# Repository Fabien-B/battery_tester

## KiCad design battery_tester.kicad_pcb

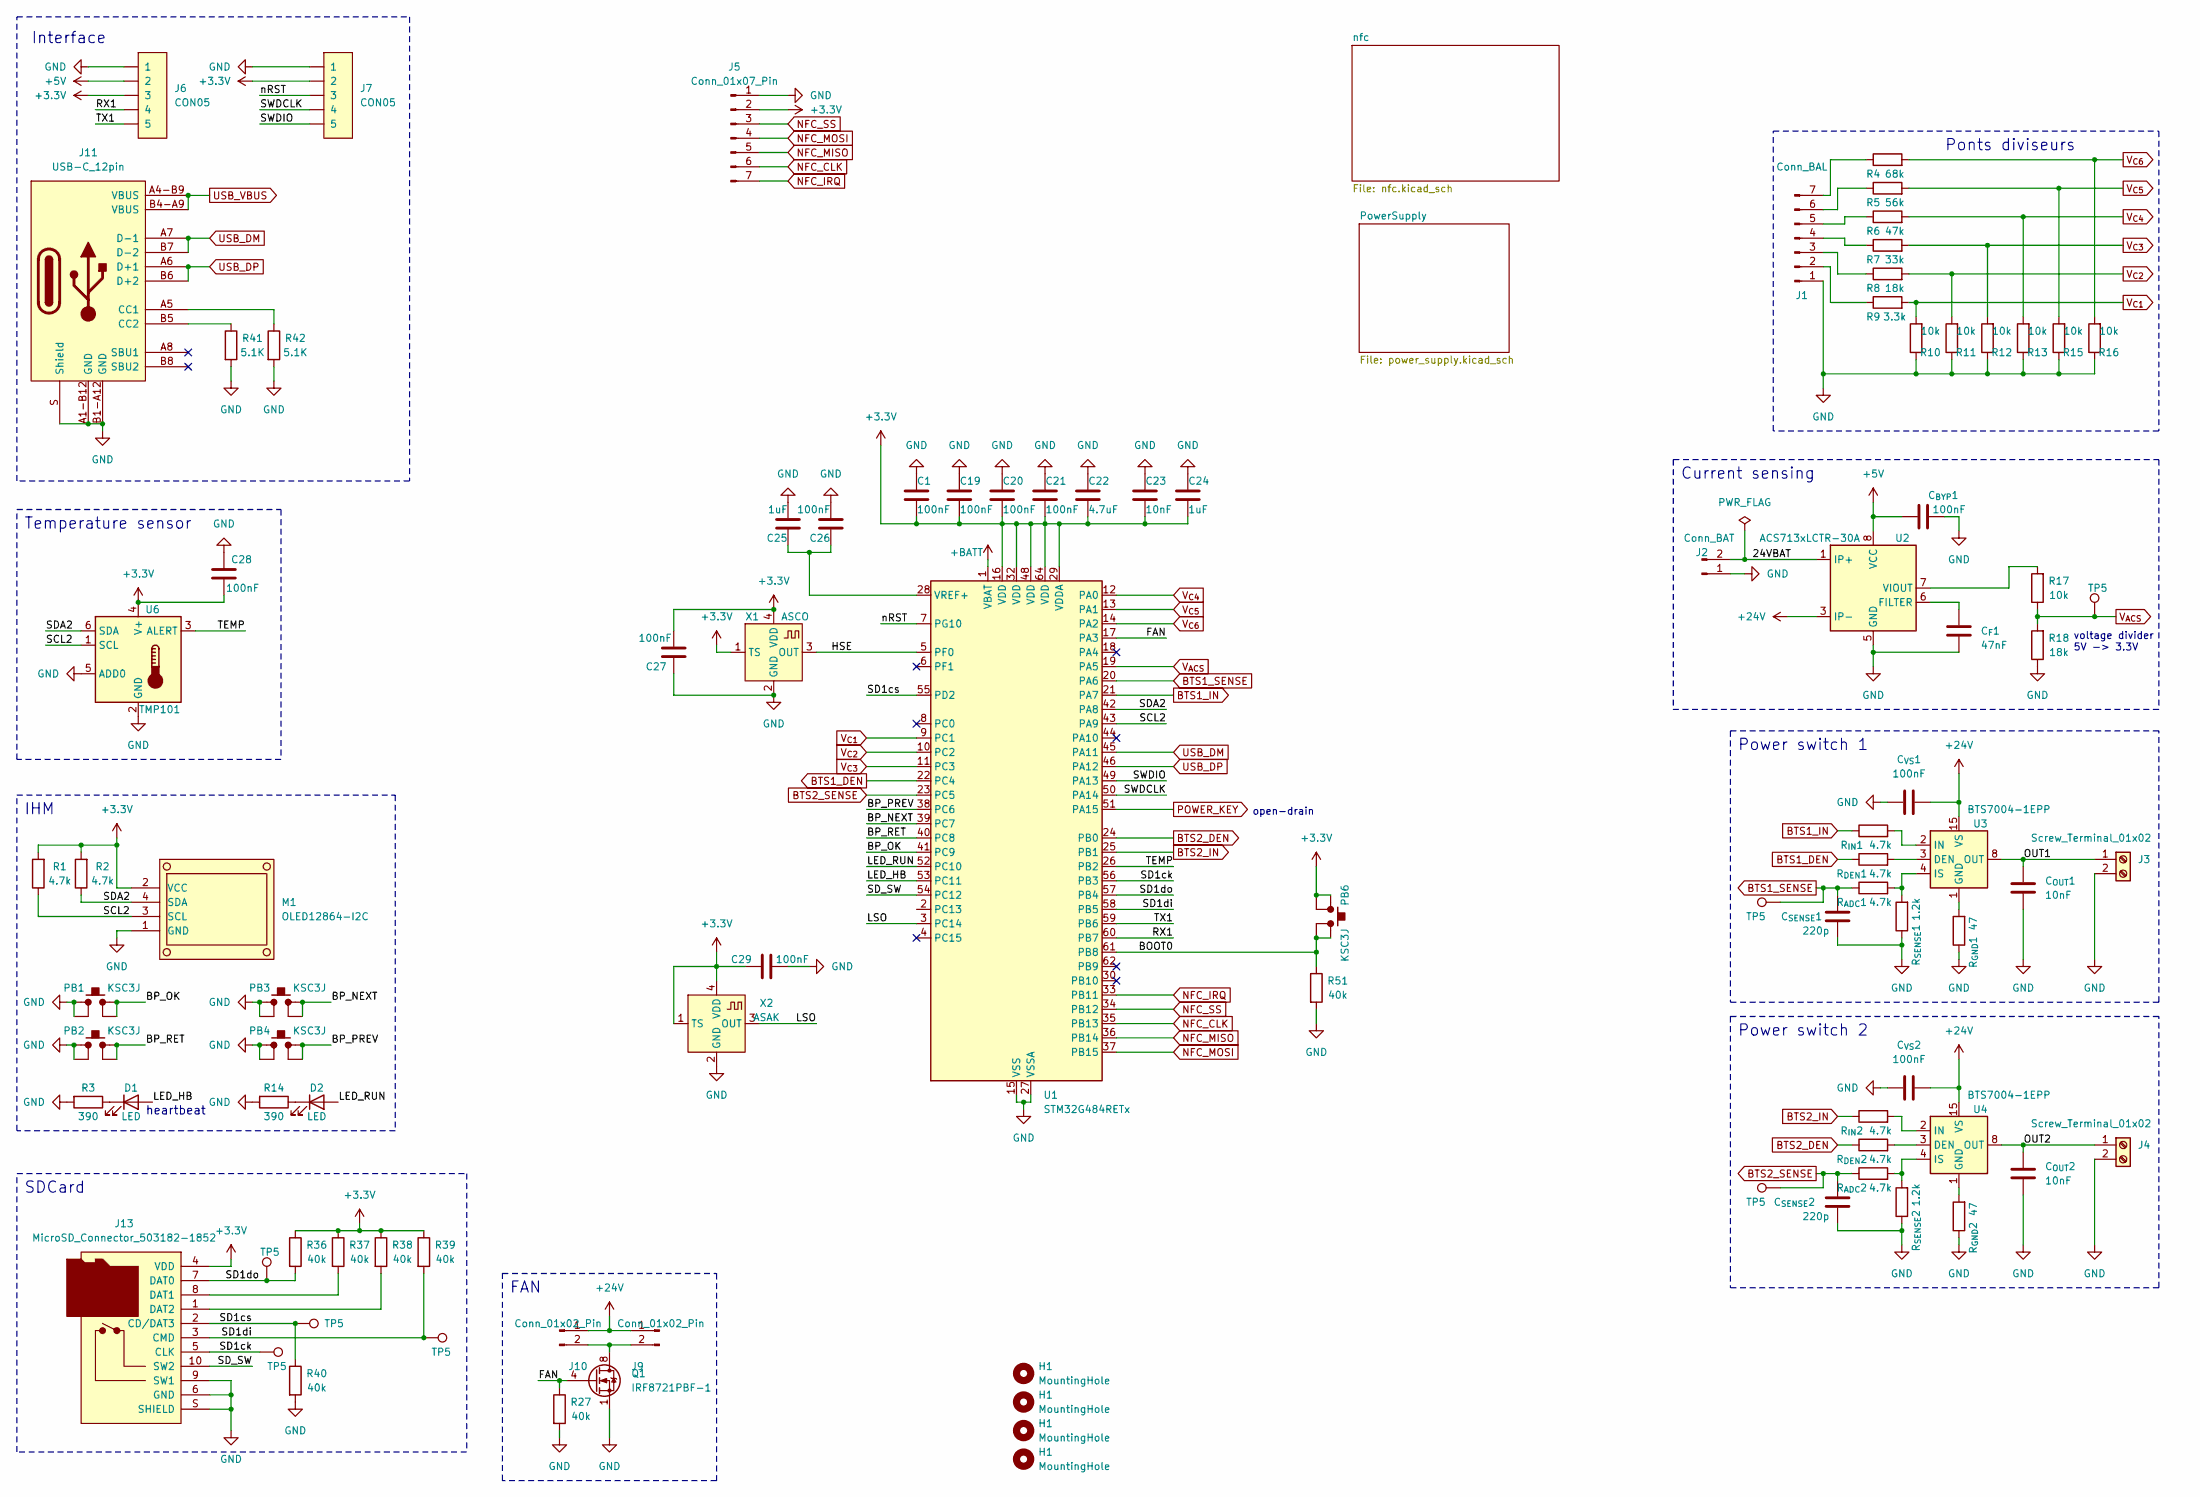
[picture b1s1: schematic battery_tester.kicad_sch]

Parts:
C1, C19, C20, C21, C26, C27, C28, C29: 100nF; C_0603_1608Metric
C22: 4.7uF; C_0603_1608Metric
C23: 10nF; C_0603_1608Metric
C24, C25: 1uF; C_0603_1608Metric
C_{BYP}1: 100nF; C_0603_1608Metric
C_{F}1: 47nF; C_0603_1608Metric
C_{OUT}1, C_{OUT}2: 10nF; C_0603_1608Metric
C_{SENSE}1, C_{SENSE}2: 220p; C_0603_1608Metric
C_{VS}1, C_{VS}2: 100nF; C_0603_1608Metric
D1, D2: LED; LED_0603_1608Metric
H1: MountingHole; MountingHole_3.2mm_M3
J1: Conn_BAL; JST_XH_S7B-XH-A_1x07_P2.50mm_Horizontal
J2: Conn_BAT; AMASS_XT60IPW-M_1x03_P7.20mm_Horizontal
J3, J4: Screw_Terminal_01x02; TerminalBlock_bornier-2_P5.08mm
J5: Conn_01x07_Pin; PicoBlade_53398-0771
J6, J7: CON05; PicoBlade_53398-0571
J9, J10: Conn_01x02_Pin; PinHeader_1x02_P2.54mm_Horizontal
J11: USB-C_12pin; USB-C_HRO_C-31-M-12
J13: MicroSD_Connector_503182-1852; MicroSD_503182-1852
M1: OLED12864-I2C
PB1, PB2, PB3, PB4, PB6: KSC3J
Q1: IRF8721PBF-1; SOIC-8_3.9x4.9mm_P1.27mm
R1, R2: 4.7k; R_0603_1608Metric
R3, R14: 390; R_0603_1608Metric
R4: 68k; R_0603_1608Metric
R5: 56k; R_0603_1608Metric
R6: 47k; R_0603_1608Metric
R7: 33k; R_0603_1608Metric
R8, R18: 18k; R_0603_1608Metric
R9: 3.3k; R_0603_1608Metric
R10, R11, R12, R13, R15, R16, R17: 10k; R_0603_1608Metric
R27, R36, R37, R38, R39, R40, R51: 40k; R_0603_1608Metric
R41, R42: 5.1K; R_0603_1608Metric
R_{ADC}1, R_{ADC}2: 4.7k; R_0603_1608Metric
R_{DEN}1, R_{DEN}2: 4.7k; R_0603_1608Metric
R_{GND}1, R_{GND}2: 47; R_0603_1608Metric
R_{IN}1, R_{IN}2: 4.7k; R_0603_1608Metric
R_{SENSE}1, R_{SENSE}2: 1.2k; R_0603_1608Metric
TP5: TestPoint; TestPoint_Pad_D2.0mm
U1: STM32G484RETx; LQFP-64_10x10mm_P0.5mm
U2: ACS713xLCTR-30A; SOIC-8_3.9x4.9mm_P1.27mm
U3, U4: BTS7004-1EPP; Infineon_PG-TSDSO-14-22
U6: TMP101; SOT-23-6
X1: ASCO; Osc_ASCO
X2: ASAK; Osc_ASAK

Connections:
+5V: C_{BYP}1.1, J6.2, U2.8 (VCC); also elsewhere on the board
+24V: C_{VS}1.1, C_{VS}2.1, J9.1, J10.1, U2.3 (IP-), U2.4 (IP-), U3.15 (VS), U4.15 (VS)
+BATT: U1.1 (VBAT); also elsewhere on the board
/24VBAT: J2.2, U2.1 (IP+), U2.2 (IP+)
/BP_NEXT: PB3.2, PB3.3, U1.39 (PC7)
/BP_OK: PB1.2, PB1.3, U1.41 (PC9)
/BP_PREV: PB4.2, PB4.3, U1.38 (PC6)
/BP_RET: PB2.2, PB2.3, U1.40 (PC8)
/FAN: Q1.4 (G), R27.1, U1.17 (PA3)
/HSE: U1.5 (PF0), X1.3 (OUT)
/LED_HB: D1.2 (A), U1.53 (PC11)
/LED_RUN: D2.2 (A), U1.52 (PC10)
/LSO: U1.3 (PC14), X2.3 (OUT)
/OUT1: C_{OUT}1.1, J3.1, U3.8 (OUT), U3.9 (OUT), U3.10 (OUT), U3.12 (OUT), U3.13 (OUT), U3.14 (OUT)
/OUT2: C_{OUT}2.1, J4.1, U4.8 (OUT), U4.9 (OUT), U4.10 (OUT), U4.12 (OUT), U4.13 (OUT), U4.14 (OUT)
/RX1: J6.4, U1.60 (PB7)
/SCL2: M1.3 (SCL), R1.1, U1.43 (PA9), U6.1 (SCL)
/SD1ck: J13.5 (CLK), U1.56 (PB3); also elsewhere on the board
/SD1cs: J13.2 (CD/DAT3), R40.1, U1.55 (PD2); also elsewhere on the board
/SD1di: J13.3 (CMD), R39.2, U1.58 (PB5); also elsewhere on the board
/SD1do: J13.7 (DAT0), R36.2, U1.57 (PB4); also elsewhere on the board
/SDA2: M1.4 (SDA), R2.1, U1.42 (PA8), U6.6 (SDA)
/SD_SW: J13.10 (SW2), U1.54 (PC12)
/SWDCLK: J7.4, U1.50 (PA14)
/SWDIO: J7.5, U1.49 (PA13)
/TEMP: U1.26 (PB2), U6.3 (ALERT)
/TX1: J6.5, U1.59 (PB6)
/nRST: J7.3, U1.7 (PG10)
BTS1_DEN: R_{DEN}1.1, U1.22 (PC4)
BTS1_IN: R_{IN}1.1, U1.21 (PA7)
BTS1_SENSE: C_{SENSE}1.1, R_{ADC}1.1, U1.20 (PA6); also elsewhere on the board
BTS2_DEN: R_{DEN}2.1, U1.24 (PB0)
BTS2_IN: R_{IN}2.1, U1.25 (PB1)
BTS2_SENSE: C_{SENSE}2.1, R_{ADC}2.1, U1.23 (PC5); also elsewhere on the board
NFC_CLK: U1.35 (PB13); also elsewhere on the board
NFC_IRQ: U1.33 (PB11); also elsewhere on the board
NFC_MISO: U1.36 (PB14); also elsewhere on the board
NFC_MOSI: U1.37 (PB15); also elsewhere on the board
NFC_SS: U1.34 (PB12); also elsewhere on the board
unnamed: D1.1 (K), R3.1
unnamed: D2.1 (K), R14.1
unnamed: J1.2, R9.1
unnamed: J1.3, R8.1
unnamed: J1.5, R6.1
unnamed: J1.6, R5.1
unnamed: J1.7, R4.1
unnamed: J9.2, J10.2, Q1.5 (D), Q1.6 (D), Q1.7 (D), Q1.8 (D)
unnamed: J11.A5 (CC1), R42.1
unnamed: J11.B5 (CC2), R41.1
unnamed: J13.8 (DAT1), R37.2
unnamed: J13.1 (DAT2), R38.2
unnamed: C_{F}1.1, U2.6 (FILTER)
unnamed: R17.2, U2.7 (VIOUT)
unnamed: R_{DEN}1.2, U3.3 (DEN)
unnamed: R_{GND}1.2, U3.1 (GND)
unnamed: R_{IN}1.2, U3.2 (IN)
unnamed: R_{ADC}1.2, R_{SENSE}1.2, U3.4 (IS)
unnamed: R_{DEN}2.2, U4.3 (DEN)
unnamed: R_{GND}2.2, U4.1 (GND)
unnamed: R_{IN}2.2, U4.2 (IN)
unnamed: R_{ADC}2.2, R_{SENSE}2.2, U4.4 (IS)
USB_DM: J11.A7 (D-1), J11.B7 (D-2), U1.45 (PA11)
USB_DP: J11.A6 (D+1), J11.B6 (D+2), U1.46 (PA12)
USB_VBUS: J11.A4-B9 (VBUS), J11.B4-A9 (VBUS); also elsewhere on the board
V_{ACS}: R17.1, R18.2, U1.19 (PA5); also elsewhere on the board
V_{C1}: R9.2, R10.2, U1.9 (PC1)
V_{C2}: R8.2, R11.2, U1.10 (PC2)
V_{C4}: R6.2, R13.2, U1.12 (PA0)
V_{C5}: R5.2, R15.2, U1.13 (PA1)
V_{C6}: R4.2, R16.2, U1.14 (PA2)

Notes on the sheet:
Interface
Power switch 1
voltage divider 5V -> 3.3V
IHM
Current sensing
SDCard
Ponts diviseurs
heartbeat
Temperature sensor
open-drain
FAN
Power switch 2

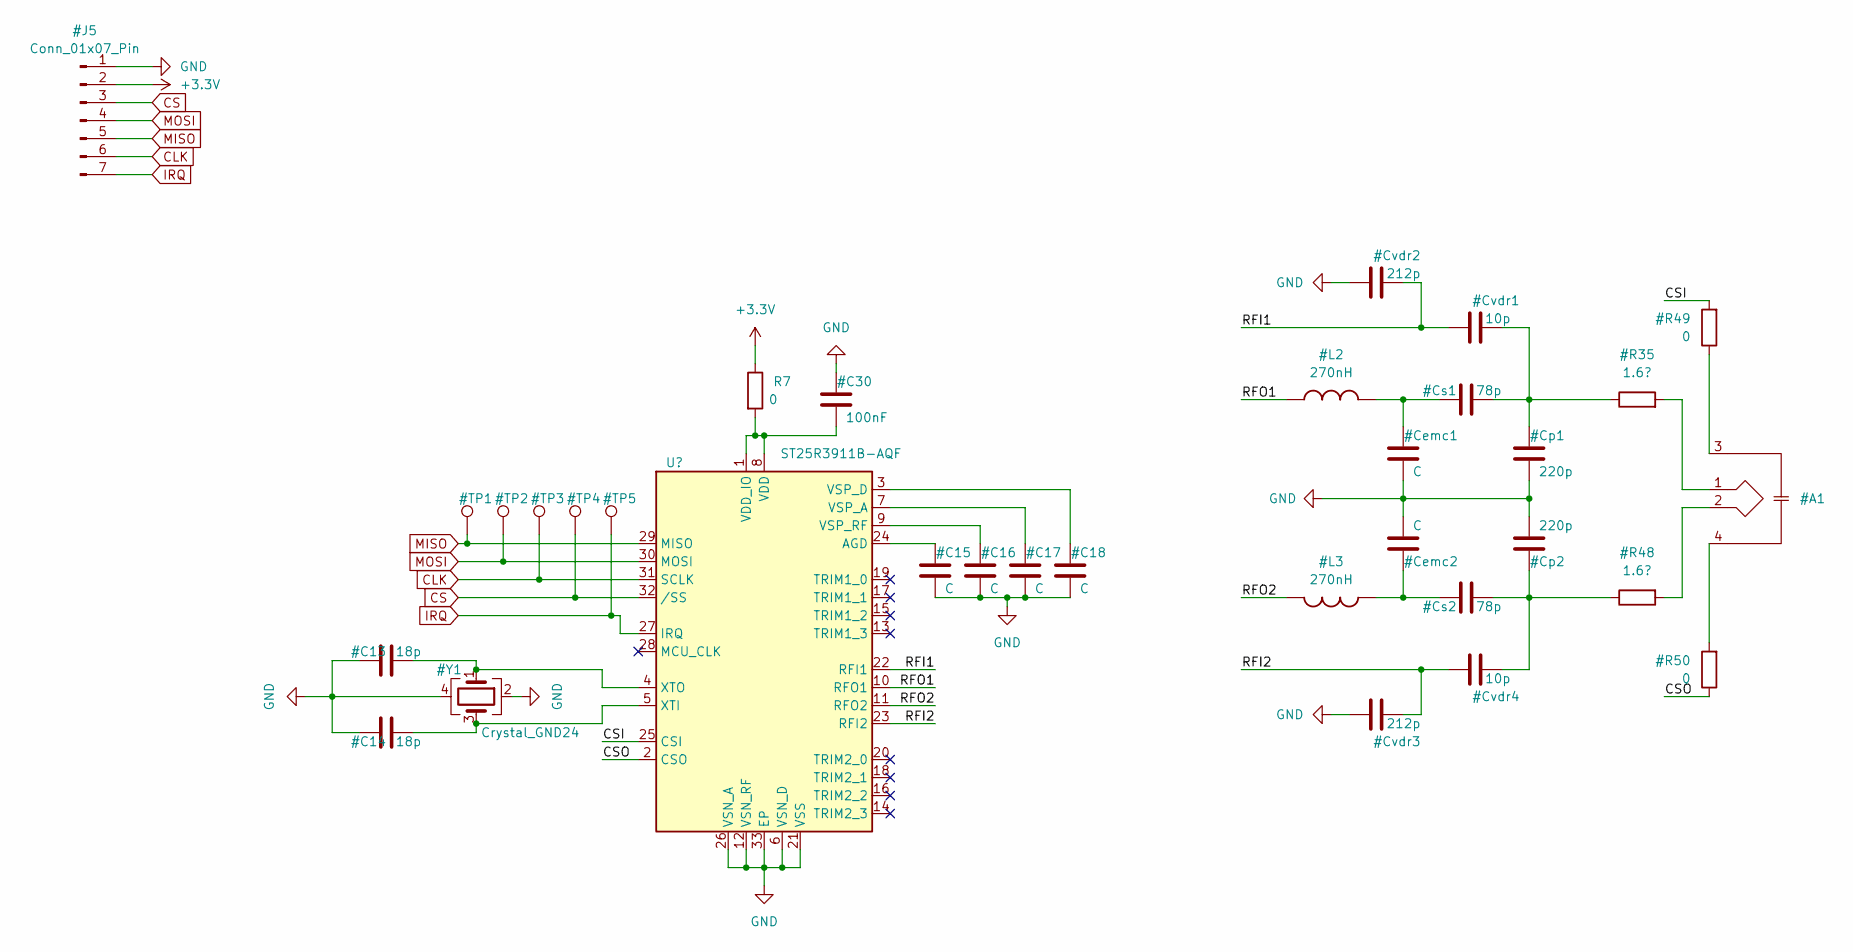
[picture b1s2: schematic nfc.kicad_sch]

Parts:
R7: 0; R_0603_1608Metric

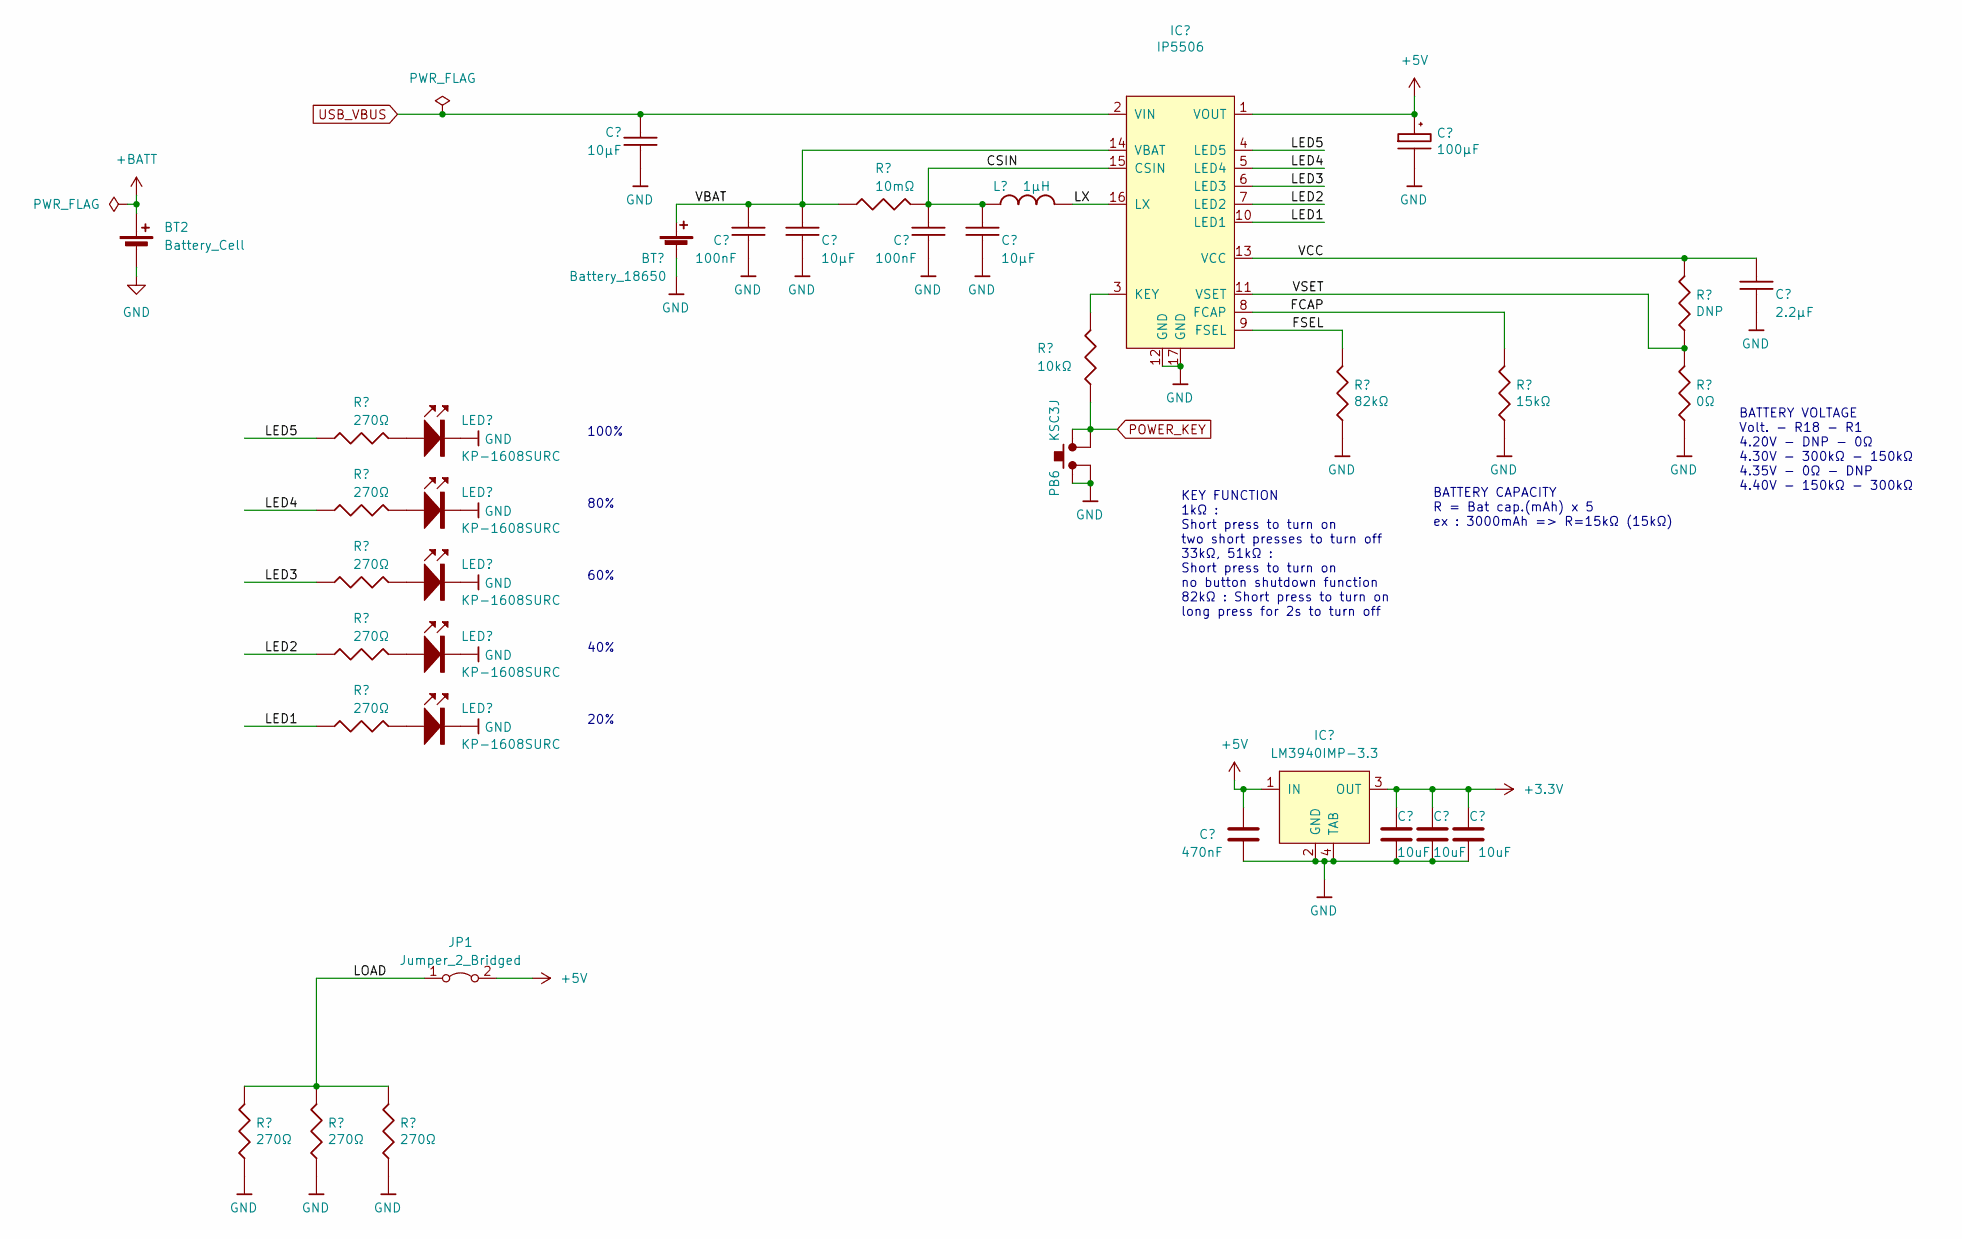
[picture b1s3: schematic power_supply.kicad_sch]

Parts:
BT1: Battery_18650; BatteryHolder_Keystone_1042_1x18650
BT2: Battery_Cell; BatteryHolder_Keystone_3002_1x2032
C2, C4, C6: 10µF; C_0603
C3, C5: 100nF; C_0603
C7: 470nF; C_0603
C8, C10, C11: 10uF; C_0603
C9: 100µF; EIA_6032-28
C12: 2.2µF; C_0603
IC1: IP5506
IC2: LM3940IMP-3.3; LM3940IMP
JP1: Jumper_2_Bridged; SolderJumper-2_P1.3mm_Open_TrianglePad1.0x1.5mm
L1: 1µH; IHLP2525CZ
LED1, LED2, LED3, LED4, LED5: KP-1608SURC
PB6: KSC3J
R19, R20, R21, R22, R23, R24, R25, R26: 270Ω; R_0603
R29: 10mΩ; R_0603
R30: 10kΩ; R_0603
R31: 82kΩ; R_0603
R32: 15kΩ; R_0603
R33: DNP; R_0603
R34: 0Ω; R_0603

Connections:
+5V: C7.1, C9.1, IC1.1 (VOUT), IC2.1 (IN), JP1.2 (B); also elsewhere on the board
+BATT: BT2.1 (+); also elsewhere on the board
/PowerSupply/CSIN: C5.1, C6.1, IC1.15 (CSIN), L1.1, R29.1
/PowerSupply/FCAP: IC1.8 (FCAP), R32.1
/PowerSupply/FSEL: IC1.9 (FSEL), R31.1
/PowerSupply/LED1: IC1.10 (LED1), R25.2
/PowerSupply/LED2: IC1.7 (LED2), R24.2
/PowerSupply/LED3: IC1.6 (LED3), R23.2
/PowerSupply/LED4: IC1.5 (LED4), R22.2
/PowerSupply/LED5: IC1.4 (LED5), R21.2
/PowerSupply/LOAD: JP1.1 (A), R19.1, R20.1, R26.1
/PowerSupply/LX: IC1.16 (LX), L1.2
/PowerSupply/VBAT: BT1.1 (+), C3.1, C4.1, IC1.14 (VBAT), R29.2
/PowerSupply/VCC: C12.1, IC1.13 (VCC), R33.1
/PowerSupply/VSET: IC1.11 (VSET), R33.2, R34.1
unnamed: IC1.3 (KEY), R30.1
unnamed: LED1.2 (A), R25.1
unnamed: LED2.2 (A), R24.1
unnamed: LED3.2 (A), R23.1
unnamed: LED4.2 (A), R22.1
unnamed: LED5.2 (A), R21.1
USB_VBUS: C2.1, IC1.2 (VIN); also elsewhere on the board

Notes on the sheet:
KEY FUNCTION 1kΩ : Short press to turn on two short presses to turn off 33kΩ, 51kΩ : Short press to turn on no button shutdown function 82kΩ : Short press to turn on long press for 2s to turn off
BATTERY CAPACITY R = Bat cap.(mAh) x 5 ex : 3000mAh => R=15kΩ (15kΩ)
40%
100%
80%
60%
20%
BATTERY VOLTAGE Volt. - R18 - R1 4.20V - DNP - 0Ω 4.30V - 300kΩ - 150kΩ 4.35V - 0Ω - DNP 4.40V - 150kΩ - 300kΩ

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
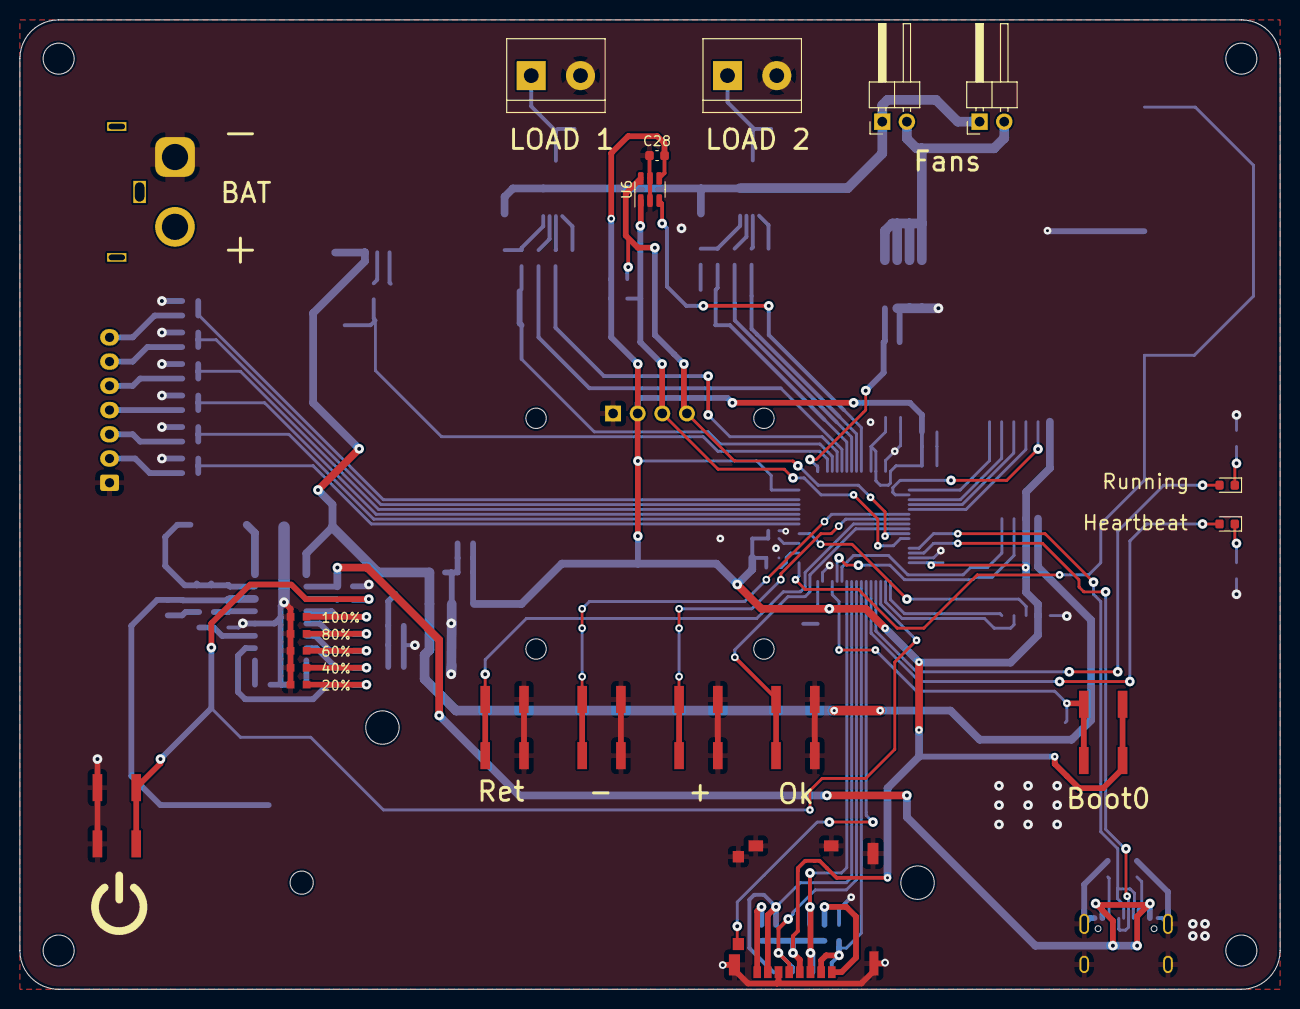
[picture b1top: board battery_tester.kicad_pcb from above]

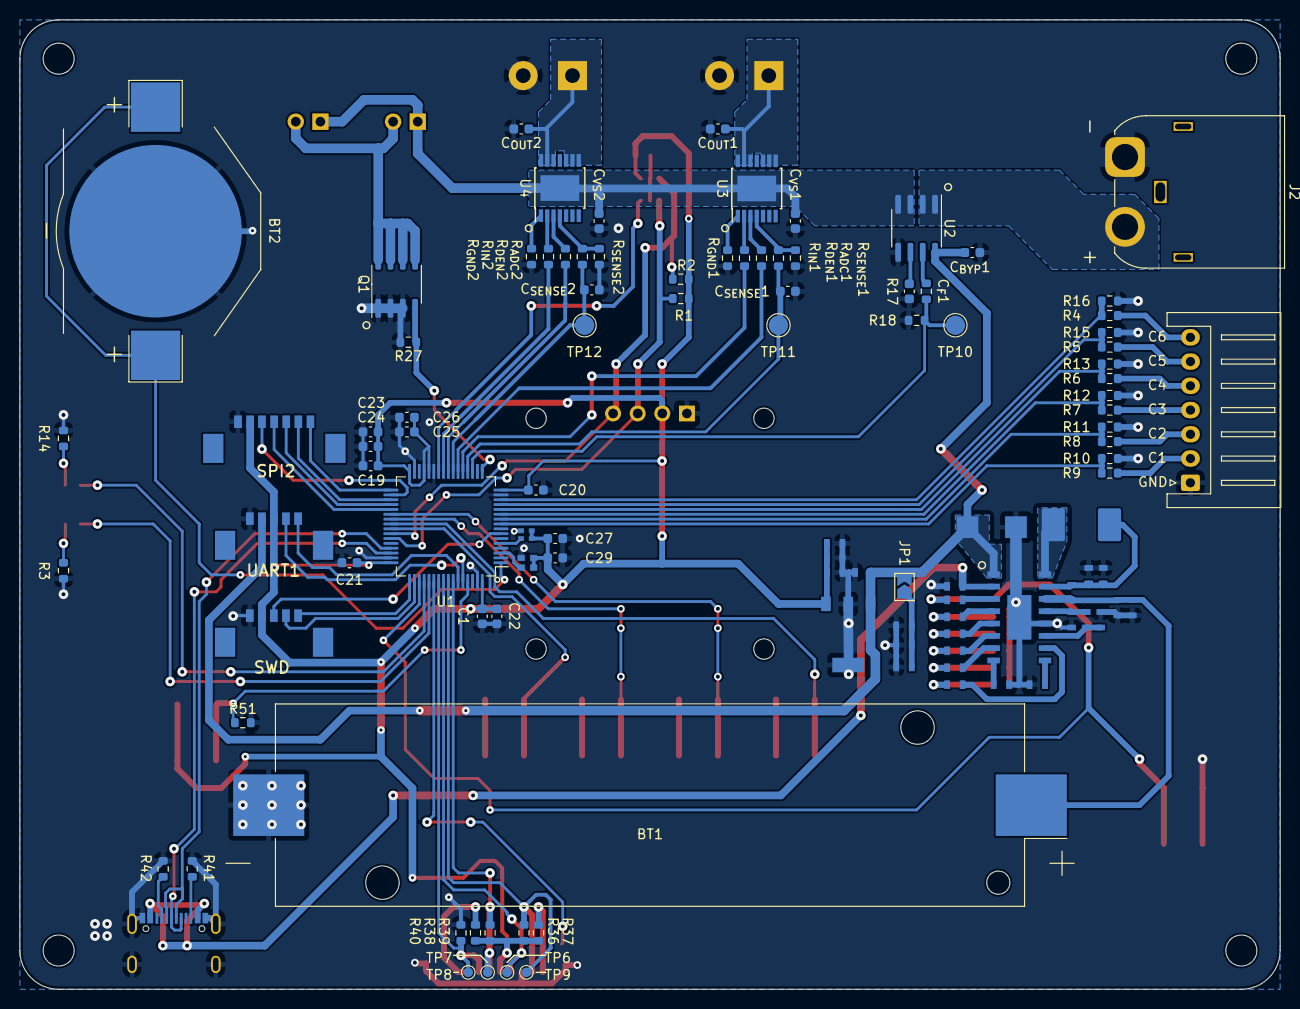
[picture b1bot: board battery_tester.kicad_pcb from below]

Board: 2 copper layers, 130.0 x 100.0 mm, 132 parts (107 on the bottom side), 95 nets.

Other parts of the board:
H2, H3, H4: MountingHole; MountingHole_3.2mm_M3
J12: Conn_01x07_Pin; PicoBlade_53398-0771
PB7: KSC3J
TP6, TP7, TP8, TP9: TestPoint; TestPoint_Pad_D1.0mm
TP10, TP11, TP12: TestPoint; TestPoint_Pad_D2.0mm

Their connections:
/SD1ck: TP6.1; also elsewhere on the board
/SD1cs: TP8.1; also elsewhere on the board
/SD1di: TP7.1; also elsewhere on the board
/SD1do: TP9.1; also elsewhere on the board
BTS1_SENSE: TP11.1; also elsewhere on the board
BTS2_SENSE: TP12.1; also elsewhere on the board
NFC_CLK: J12.6; also elsewhere on the board
NFC_IRQ: J12.7; also elsewhere on the board
NFC_MISO: J12.5; also elsewhere on the board
NFC_MOSI: J12.4; also elsewhere on the board
NFC_SS: J12.3; also elsewhere on the board
V_{ACS}: TP10.1; also elsewhere on the board

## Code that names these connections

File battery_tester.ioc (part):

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Mcu.Name=STM32G484RETx
Mcu.Package=LQFP64
Mcu.UserName=STM32G484RETx
PA0.GPIOParameters=GPIO_Label
PA0.GPIO_Label=Vc4
PA0.Mode=IN1-Single-Ended
PA0.Signal=ADC1_IN1
PA1.GPIOParameters=GPIO_Label
PA1.GPIO_Label=Vc5
PA1.Mode=IN2-Single-Ended
PA1.Signal=ADC1_IN2
PA11.Mode=Device
PA11.Signal=USB_DM
PA12.Mode=Device
PA12.Signal=USB_DP
PA13.Mode=Serial_Wire
PA13.Signal=SYS_JTMS-SWDIO
PA14.Mode=Serial_Wire
PA14.Signal=SYS_JTCK-SWCLK
PA15.GPIOParameters=PinState,GPIO_PuPd,GPIO_Label,GPIO_ModeDefaultOutputPP
PA15.GPIO_Label=POWER_KEY
PA15.GPIO_ModeDefaultOutputPP=GPIO_MODE_OUTPUT_OD
PA15.GPIO_PuPd=GPIO_NOPULL
PA15.PinState=GPIO_PIN_SET
PA15.Signal=GPIO_Output
PA2.GPIOParameters=GPIO_Label
PA2.GPIO_Label=Vc6
PA2.Mode=IN3-Single-Ended
PA2.Signal=ADC1_IN3
PA3.GPIOParameters=GPIO_Label
PA3.GPIO_Label=FAN
PA3.Signal=S_TIM2_CH4
PA5.GPIOParameters=GPIO_Label
PA5.GPIO_Label=Vacs
PA5.Mode=IN13-Single-Ended
PA5.Signal=ADC2_IN13
PA6.GPIOParameters=GPIO_Label
PA6.GPIO_Label=BTS1_sense
PA6.Mode=IN3-Single-Ended
PA6.Signal=ADC2_IN3
PA7.GPIOParameters=GPIO_Label
PA7.GPIO_Label=BTS1_IN
PA7.Signal=S_TIM3_CH2
PA8.Mode=I2C
PA8.Signal=I2C2_SDA
PA9.Mode=I2C
PA9.Signal=I2C2_SCL
PB0.GPIOParameters=GPIO_Label
PB0.GPIO_Label=BTS2_DEN
PB0.Signal=GPIO_Output
PB1.GPIOParameters=GPIO_Label
PB1.GPIO_Label=BTS2_IN
PB1.Signal=S_TIM3_CH4
PB11.GPIOParameters=GPIO_Label
PB11.GPIO_Label=NFC_IRQ
PB11.Signal=GPIO_Input
PB12.GPIOParameters=GPIO_Label
PB12.GPIO_Label=NFC_CS
PB12.Mode=NSS_Signal_Hard_Output
PB12.Signal=SPI2_NSS
PB13.GPIOParameters=GPIO_Label
PB13.GPIO_Label=NFC_CLK
PB13.Mode=Full_Duplex_Master
PB13.Signal=SPI2_SCK
PB14.GPIOParameters=GPIO_Label
PB14.GPIO_Label=NFC_MISO
PB14.Mode=Full_Duplex_Master
PB14.Signal=SPI2_MISO
PB15.GPIOParameters=GPIO_Label
PB15.GPIO_Label=NFC_MOSI
PB15.Mode=Full_Duplex_Master
PB15.Signal=SPI2_MOSI
PB2.GPIOParameters=GPIO_Label
PB2.GPIO_Label=TEMP_ALERT
PB2.Signal=GPIO_Input
PB3.GPIOParameters=GPIO_Label
PB3.GPIO_Label=SD_CLK
PB3.Mode=Full_Duplex_Master
PB3.Signal=SPI1_SCK
PB4.GPIOParameters=GPIO_Label
PB4.GPIO_Label=SD_MISO
PB4.Mode=Full_Duplex_Master
PB4.Signal=SPI1_MISO
PB5.GPIOParameters=GPIO_Label
PB5.GPIO_Label=SD_MOSI
PB5.Mode=Full_Duplex_Master
PB5.Signal=SPI1_MOSI
PB6.Mode=Asynchronous
PB6.Signal=USART1_TX
PB7.Mode=Asynchronous
PB7.Signal=USART1_RX
PB8-BOOT0.GPIOParameters=GPIO_Label
PB8-BOOT0.GPIO_Label=BOOT0
PB8-BOOT0.Signal=GPIO_Input
PC1.GPIOParameters=GPIO_Label
PC1.GPIO_Label=Vc1
PC1.Mode=IN7-Single-Ended
PC1.Signal=ADC1_IN7
PC10.GPIOParameters=GPIO_Label
PC10.GPIO_Label=LED_RUN
PC10.Signal=GPIO_Output
PC11.GPIOParameters=GPIO_Label
PC11.GPIO_Label=LED_HB
PC11.Signal=GPIO_Output
PC12.GPIOParameters=GPIO_Label
PC12.GPIO_Label=SD_DETECT
PC12.Signal=GPIO_Output
PC14-OSC32_IN.Mode=LSE-External-Clock-Source
PC14-OSC32_IN.Signal=RCC_OSC32_IN
PC2.GPIOParameters=GPIO_Label
PC2.GPIO_Label=Vc2
PC2.Mode=IN8-Single-Ended
PC2.Signal=ADC1_IN8
PC3.GPIOParameters=GPIO_Label
PC3.GPIO_Label=Vc3
PC3.Mode=IN9-Single-Ended
PC3.Signal=ADC1_IN9
PC4.GPIOParameters=GPIO_Label
PC4.GPIO_Label=BTS1_DEN
PC4.Signal=GPIO_Output
PC5.GPIOParameters=GPIO_Label
PC5.GPIO_Label=BTS2_sense
PC5.Mode=IN11-Single-Ended
PC5.Signal=ADC2_IN11
PC6.GPIOParameters=GPIO_Label
PC6.GPIO_Label=BP_PREV
PC6.Signal=GPIO_Input
PC7.GPIOParameters=GPIO_Label
PC7.GPIO_Label=BP_NEXT
PC7.Signal=GPIO_Input
PC8.GPIOParameters=GPIO_Label
PC8.GPIO_Label=BP_RET
PC8.Signal=GPIO_Input
PC9.GPIOParameters=GPIO_Label
PC9.GPIO_Label=BP_OK
PC9.Signal=GPIO_Input
PD2.GPIOParameters=GPIO_Label
PD2.GPIO_Label=SD_CS
PD2.Signal=GPIO_Output
PF0-OSC_IN.Mode=HSE-External-Clock-Source
PF0-OSC_IN.Signal=RCC_OSC_IN
PG10-NRST.GPIOParameters=GPIO_Label
PG10-NRST.GPIO_Label=nRST
PG10-NRST.Signal=GPIO_Input
RCC.HSE_VALUE=8000000
RCC.SYSCLKFreq_VALUE=144000000
RCC.SYSCLKSource=RCC_SYSCLKSOURCE_PLLCLK
board=custom

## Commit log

2023-10-06 Add libs
2023-10-06 initial design
2023-10-10 Almost finalize schematics
2023-10-13 Finish layout.
2023-10-13 Set title
2023-11-10 resistors values
2023-11-10 tune clock
2023-11-11 Add missing VRef connection to 3V3.
2024-01-11 Initial ChibiOS project
2024-02-22 enable debug
2024-02-22 Add console
2024-02-22 Voltage monitoring OK
2024-02-23 Ui, power switch and begin current measurement.
2024-02-23 vscode conf
2024-07-01 stuff before change of strategy
2024-07-03 current sensing and reportting
2024-07-03 sd card
2024-08-26 begin screens
